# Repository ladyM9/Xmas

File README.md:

# Xmas ornament
A Xmas ornament based on the STM32C011F6 microcontroller.

This project is inspired schematics for Xmas ornament by Borna Biro.

## ***Commponets for project:***
-  STM32C011F6
-  WS2812B
-  Buzzer
-  JST connector
-  C type connector
-  Buttons

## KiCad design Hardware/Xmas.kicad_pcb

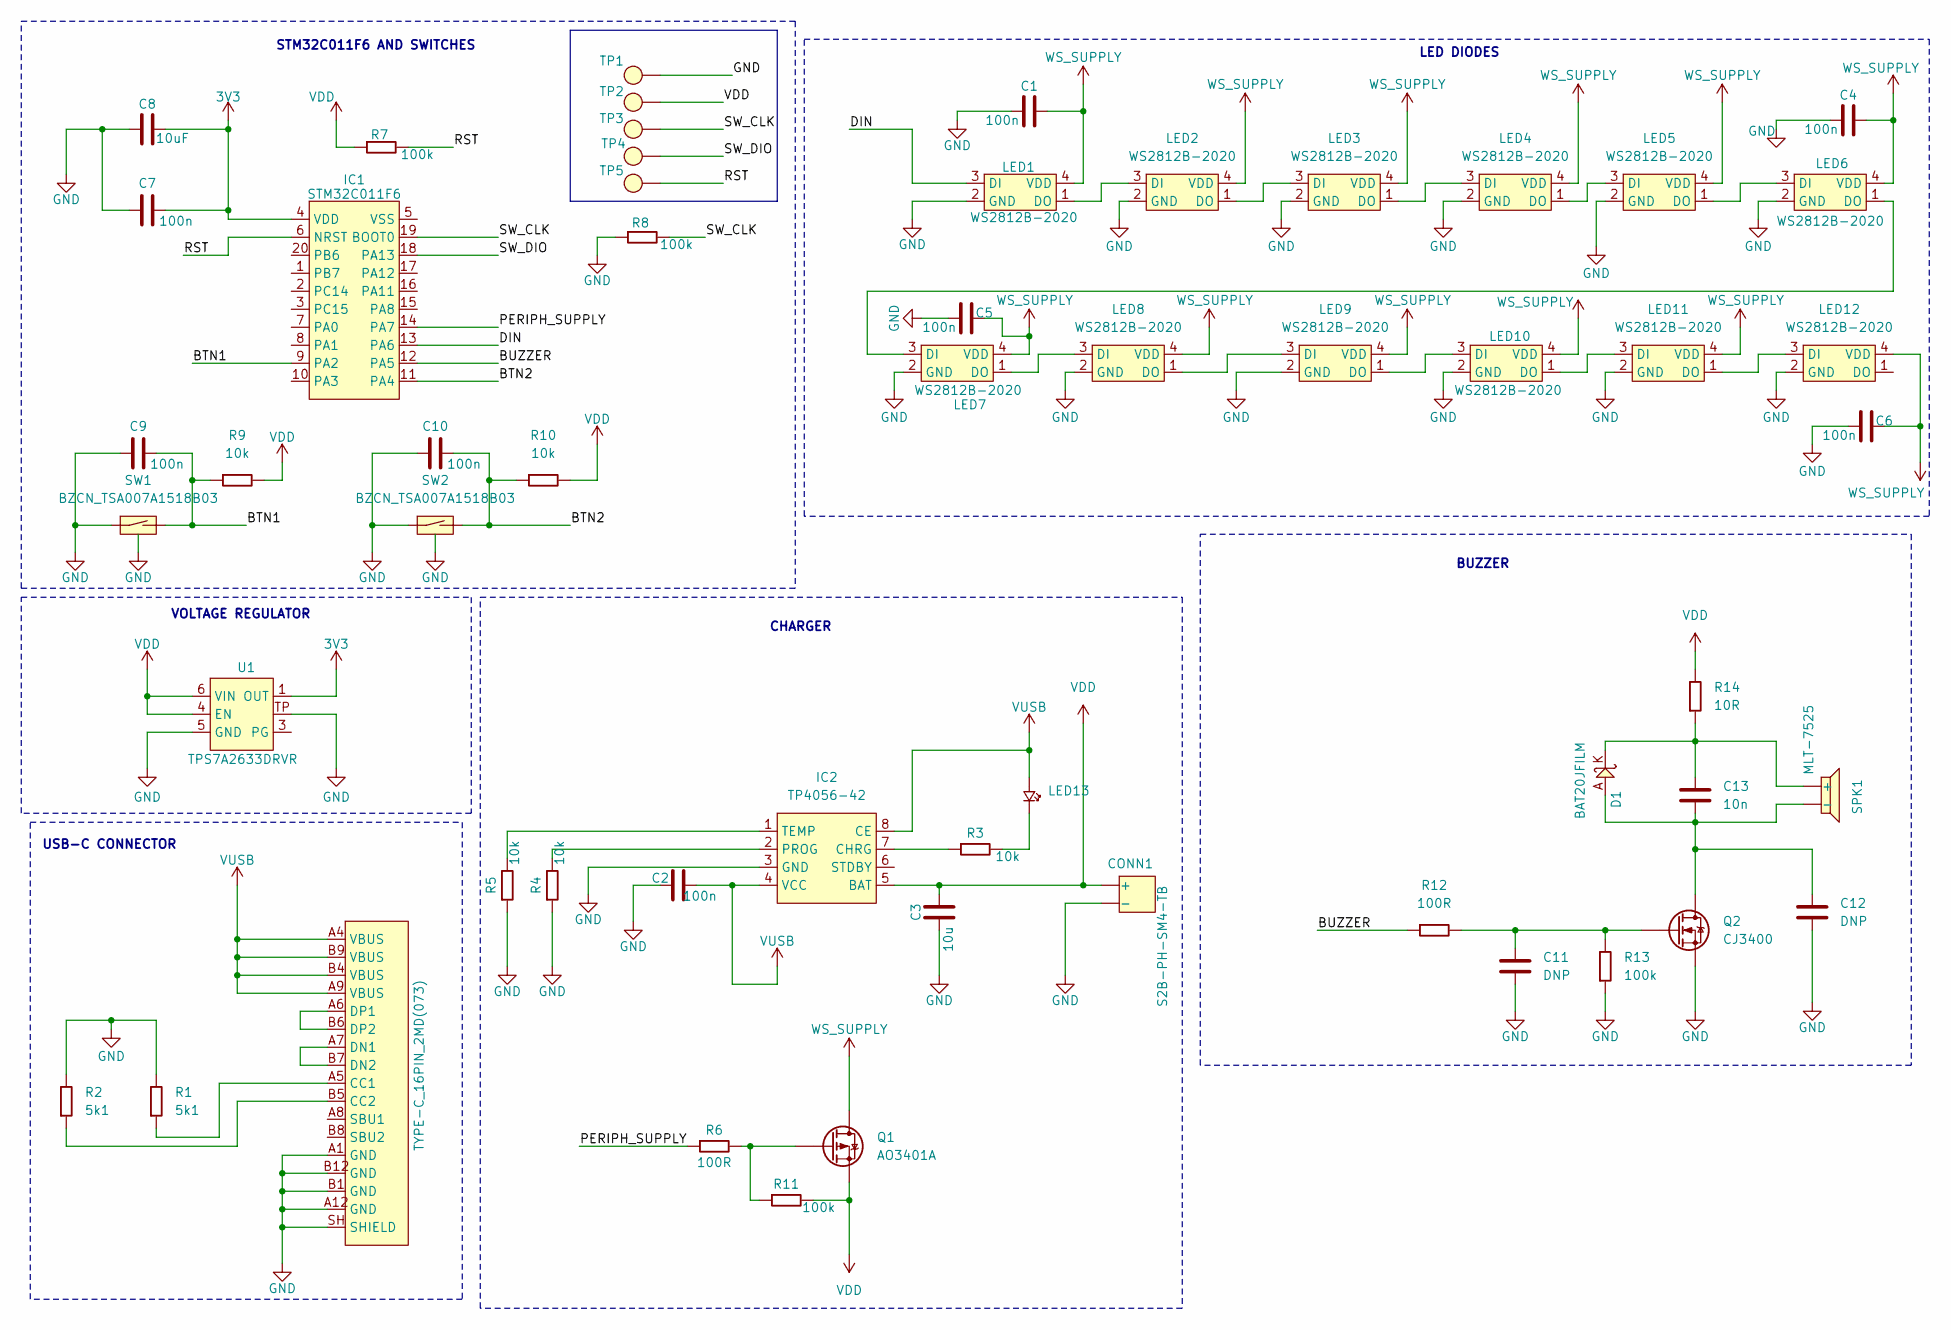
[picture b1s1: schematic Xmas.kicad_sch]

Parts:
C1, C2, C4, C5, C6, C7, C9, C10: 100n; C0603
C3: 10u; C1206
C8: 10uF; C1206
C11, C12: DNP; C0603
C13: 10n; C0603
CONN1: S2B-PH-SM4-TB; JST_S2B-PH-SM4-TB
CONN2: TYPE-C_16PIN_2MD(073)
D1: BAT20JFILM; SOD323
IC1: STM32C011F6; TSSOP20
IC2: TP4056-42; EMSOP
LED1, LED2, LED3, LED4, LED5, LED6, LED7, LED8, LED9, LED10, LED11, LED12: WS2812B-2020
LED13: LED_0603
Q1: AO3401A; SOT-23-3L
Q2: CJ3400; SOT-23-3L
R1, R2: 5k1; R0603
R3, R4, R5, R9, R10: 10k; R0603
R6, R12: 100R; R0603
R7, R8, R11, R13: 100k; R0603
R14: 10R; R0603
SPK1: MLT-7525; MTL-7525
SW1, SW2: BZCN_TSA007A1518B03; TSA007A1518B03
TP1, TP2, TP3, TP4, TP5: TP-1_5mm
U1: TPS7A2633DRVR; WSON-6

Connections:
3V3: C7.2, C8.2, IC1.4 (VDD), U1.1 (OUT)
/BTN1: C9.2, IC1.9 (PA2), R9.1, SW1.2 (SW2)
/BTN2: C10.2, IC1.11 (PA4), R10.1, SW2.2 (SW2)
/BUZZER: IC1.12 (PA5), R12.1
/DIN: IC1.13 (PA6), LED1.3 (DI)
/PERIPH_SUPPLY: IC1.14 (PA7), R6.1
/RST: IC1.6 (NRST), R7.2, TP5.1 (TP)
/SW_CLK: IC1.19 (BOOT0), R8.2, TP3.1 (TP)
/SW_DIO: IC1.18 (PA13), TP4.1 (TP)
GND: C1.1, C2.1, C3.1, C4.1, C5.1, C6.1, C7.1, C8.1, C9.1, C10.1, C11.1, C12.1, CONN1.-, CONN2.A1 (GND), CONN2.A12 (GND), CONN2.B1 (GND), CONN2.B12 (GND), CONN2.SH (SHIELD), IC2.3 (GND), LED1.2 (GND), LED2.2 (GND), LED3.2 (GND), LED4.2 (GND), LED5.2 (GND), LED6.2 (GND), LED7.2 (GND), LED8.2 (GND), LED9.2 (GND), LED10.2 (GND), LED11.2 (GND), LED12.2 (GND), Q2.3 (S), R1.2, R2.2, R4.1, R5.1, R8.1, R13.1, SW1.1 (SW1), SW1.PAD, SW2.1 (SW1), SW2.PAD, TP1.1 (TP), U1.5 (GND), U1.TP
unnamed: C13.2, D1.K, R14.1, SPK1.+
unnamed: CONN2.A5 (CC1), R1.1
unnamed: CONN2.B5 (CC2), R2.1
unnamed: CONN2.A7 (DN1), CONN2.B7 (DN2)
unnamed: CONN2.A6 (DP1), CONN2.B6 (DP2)
unnamed: IC2.7 (CHRG), R3.1
unnamed: IC2.2 (PROG), R4.2
unnamed: IC2.1 (TEMP), R5.2
unnamed: LED1.1 (DO), LED2.3 (DI)
unnamed: LED2.1 (DO), LED3.3 (DI)
unnamed: LED3.1 (DO), LED4.3 (DI)
unnamed: LED4.1 (DO), LED5.3 (DI)
unnamed: LED5.1 (DO), LED6.3 (DI)
unnamed: LED6.1 (DO), LED7.3 (DI)
unnamed: LED7.1 (DO), LED8.3 (DI)
unnamed: LED8.1 (DO), LED9.3 (DI)
unnamed: LED9.1 (DO), LED10.3 (DI)
unnamed: LED10.1 (DO), LED11.3 (DI)
unnamed: LED11.1 (DO), LED12.3 (DI)
unnamed: LED13.2 (K), R3.2
unnamed: Q1.1 (G), R6.2, R11.1
unnamed: C12.2, C13.1, D1.A, Q2.2 (D), SPK1.-
unnamed: C11.2, Q2.1 (G), R12.2, R13.2
VDD: C3.2, CONN1.+, IC2.5 (BAT), Q1.3 (S), R7.1, R9.2, R10.2, R11.2, R14.2, TP2.1 (TP), U1.4 (EN), U1.6 (VIN)
VUSB: C2.2, CONN2.A4 (VBUS), CONN2.A9 (VBUS), CONN2.B4 (VBUS), CONN2.B9 (VBUS), IC2.4 (VCC), IC2.8 (CE), LED13.1 (A)
WS_SUPPLY: C1.2, C4.2, C5.2, C6.2, LED1.4 (VDD), LED2.4 (VDD), LED3.4 (VDD), LED4.4 (VDD), LED5.4 (VDD), LED6.4 (VDD), LED7.4 (VDD), LED8.4 (VDD), LED9.4 (VDD), LED10.4 (VDD), LED11.4 (VDD), LED12.4 (VDD), Q1.2 (D)

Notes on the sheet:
BUZZER
CHARGER
STM32C011F6 AND SWITCHES
LED DIODES
VOLTAGE REGULATOR
USB-C CONNECTOR

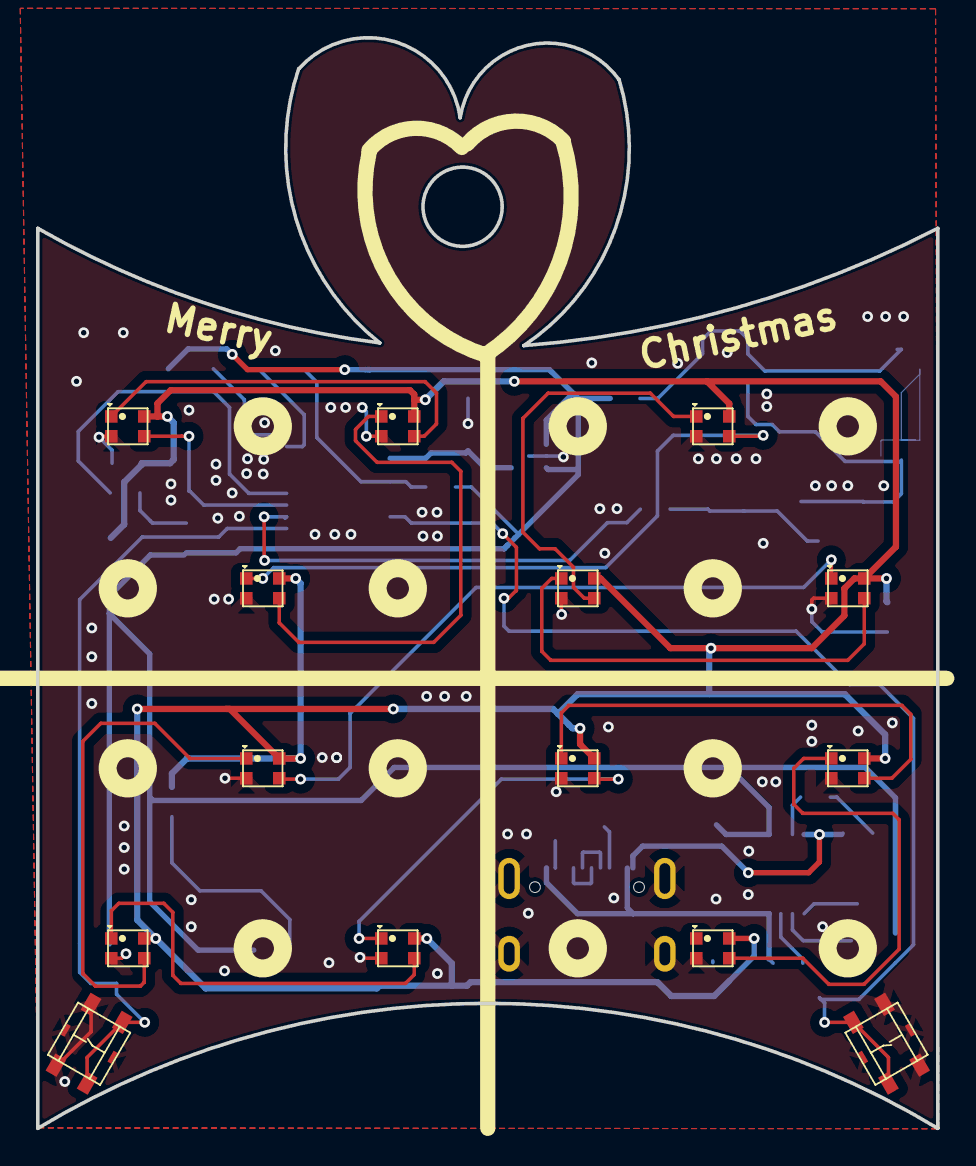
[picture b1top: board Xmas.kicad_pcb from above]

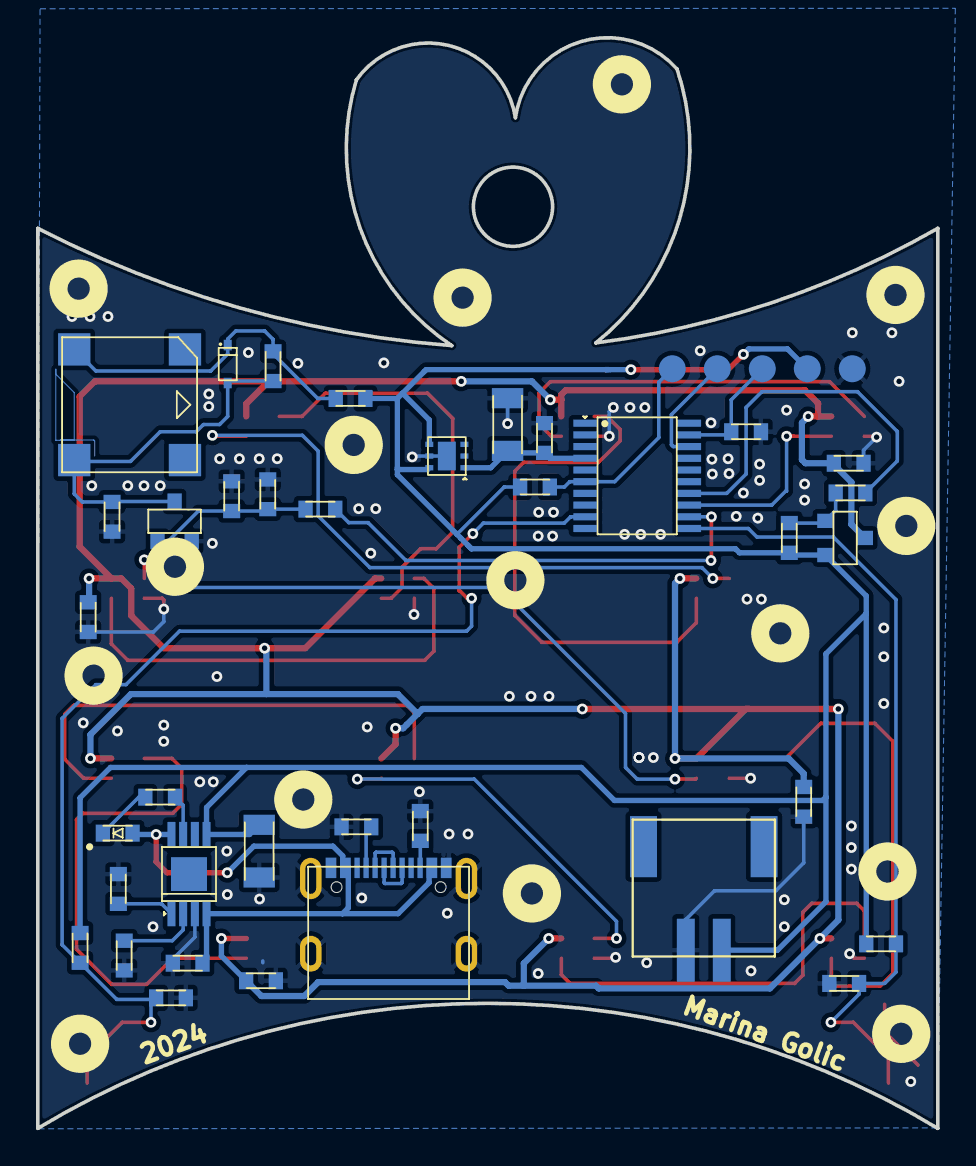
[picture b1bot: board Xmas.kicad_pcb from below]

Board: 2 copper layers, 50.0 x 60.6 mm, 56 parts (42 on the bottom side), 36 nets.

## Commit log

2024-12-04 The schematic is complete
2024-12-04 Update PCB
2024-12-05 Everything on the PCB is connected
2024-12-07 Connected uncotected traces/Marina
2024-12-07 Fixed paths in project files.
2024-12-08 Update footprints and PCB have 3D models of components
2024-12-08 PCB is finished
2024-12-09 Added Gerber file
2025-01-08 Added code for Xmas Ornament
2025-01-14 Melody is work correctly
2025-01-16 I have started writing a library for WS2812B Leds
2025-01-17 Leds working- MARINA
2025-01-23 Code is not working
2025-01-24 LEDs after filled buffer has not working
2025-01-25 One LED is working with help shift bits and timer_pwm method
2025-01-27 One LED is working with help DMA_PWM method
2025-01-27 Problem with send data of LEDs on DMA
2025-01-28 Red and green color has ok, but blue is not ok
2025-01-29 R,G and B color working corretcly
2025-01-30 The color selection option is working correctly
2025-01-30 File organization
2025-02-05 All leds light the same color
2025-02-05 All leds light at the same color
2025-02-06 New way send color on LEDs
2025-02-07 LEDs are lighting on different colors, but have a problem
2025-02-12 Control LEDs with second DMA method
2025-02-19 New way to send color on LEDS
2025-02-20 Fixed bugs on a new way to send colors to LEDs
2025-02-21 Created a library for LEDs
2025-02-28 Added animations
